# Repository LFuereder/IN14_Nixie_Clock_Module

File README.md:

# IN14-Nixie Tube Clock Module
This project contains the schematics, software implementation and documentation for a clock displaying the current time on nixie-tubes. The clock utilizes a GigaDevices GD32L233 microcontroller (ARM Cortex-M33), which triggers the displayed digits in the tubes via voltage-domain separation through LTV-352T optocouplers. 

The current design is planned to display hours and minutes, but it can be extended to display the seconds as well. 

The general structure of the project is as follows:
```
IN14_Nixie_Clock_Module/
|-- 01_Circuit_Board/
|-- 02_Software/
|-- 03_Datasheets/
```
In the folder `01_Circuit_Board` you can find all relevant files for the hardware part of this project. This includes the KiCAD project, footprints for the custom components and the CAD script for the custom tube socket. In folder `02_Software` you can find the implementation of the clock. As this is a module, the Board can be used as standalone application (although this does not make much sense, since you need at least two PCBs to display the current time) or as a set of two to display hour and minutes. A clock consisting of three boards is currently not supported, but can be extended in the future. Lastly in `03_Datasheets` you can find further information about the components in use. 

# Finished Prototype
The current prototype of a finished implementation of the clock is displayed in the figure below.

For the wiring between the modules and the DCDC-converter please consider the following image:

Since this is a prototype, we used dupont crimp connectors and wago cage clamps. In a finished product these could be replaced by fixed/soldered wires.

# Contributing
I would like to thank [@LStromaier](https://github.com/LStrohmaier) for working along side me on this project and reviewing most of the hardware and software implemenatations.

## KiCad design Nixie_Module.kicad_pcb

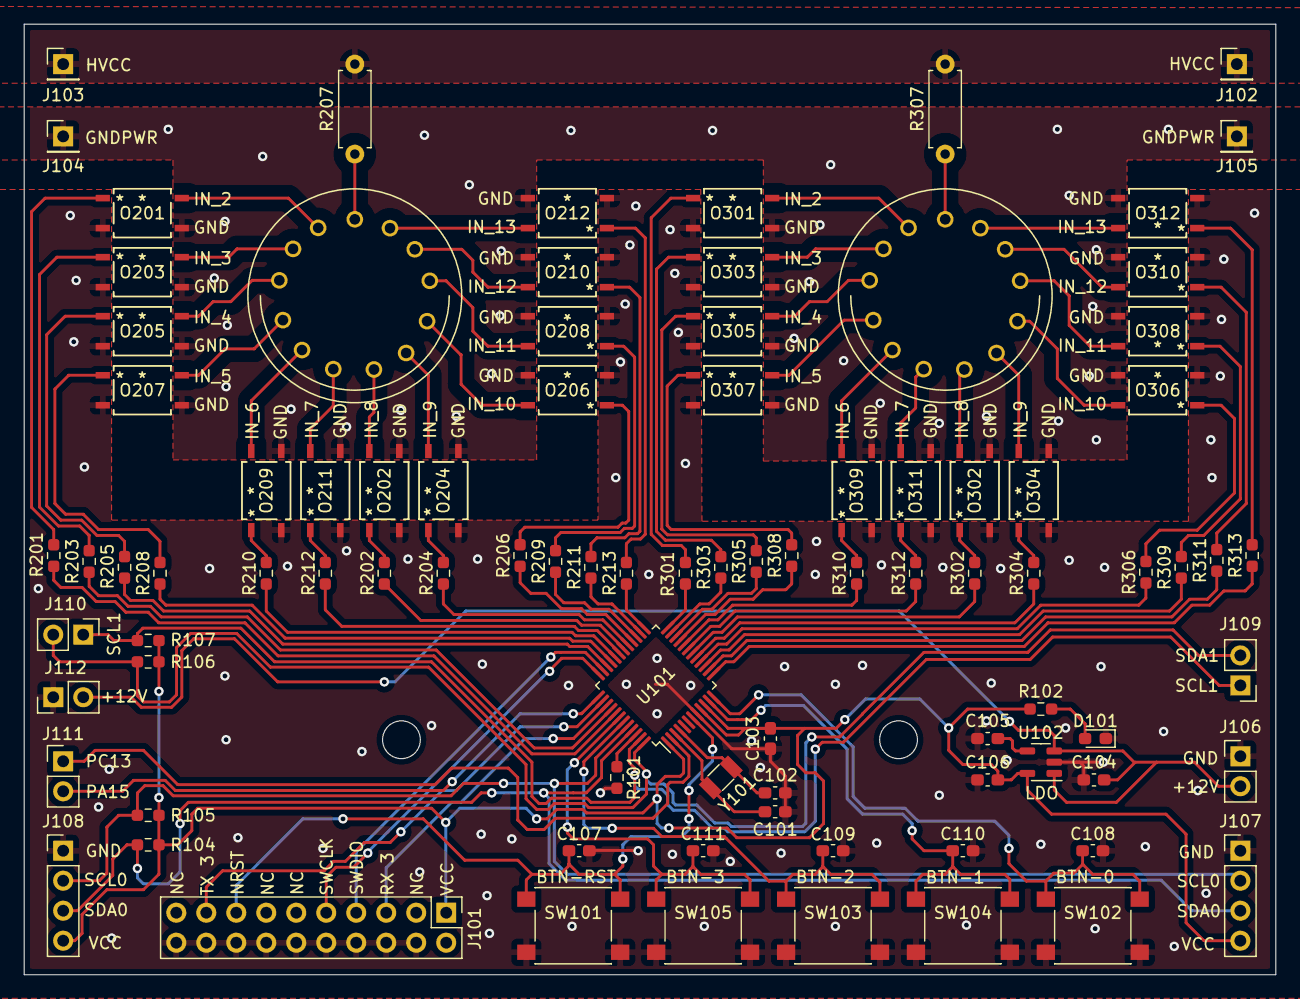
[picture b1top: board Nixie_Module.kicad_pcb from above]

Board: 2 copper layers, 106.0 x 80.5 mm, 90 parts (0 on the bottom side), 99 nets.

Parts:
C101, C102, C103, C104, C106, C107, C108, C109, C110, C111: 1u; C_0603_1608Metric_Pad1.08x0.95mm_HandSolder
C105: 470p; C_0603_1608Metric_Pad1.08x0.95mm_HandSolder
D101: LED; D_0603_1608Metric_Pad1.05x0.95mm_HandSolder
J101: JTAG_CON; PinHeader_2x10_P2.54mm_Vertical
J102: HV-IN; PinHeader_1x01_P2.54mm_Vertical
J103: HV-OUT; PinHeader_1x01_P2.54mm_Vertical
J104: HVGND-OUT; PinHeader_1x01_P2.54mm_Vertical
J105: HVGND-IN; PinHeader_1x01_P2.54mm_Vertical
J106: 12V-OUT; PinHeader_1x02_P2.54mm_Vertical
J107: Prime-CON-IN; PinHeader_1x04_P2.54mm_Vertical
J108: Prime-CON-OUT; PinHeader_1x04_P2.54mm_Vertical
J109: Sec-CON-IN; PinHeader_1x02_P2.54mm_Vertical
J110: Sec-CON-OUT; PinHeader_1x02_P2.54mm_Vertical
J111: GPIO_Con; PinHeader_1x02_P2.54mm_Vertical
J112: 12V-IN; PinHeader_1x02_P2.54mm_Vertical
O201, O202, O203, O204, O205, O206, O207, O208, O209, O210, O211, O212, O301, O302, O303, O304, O305, O306, O307, O308, O309, O310, O311, O312: LTV-352T; IC4_LTV-352T_LTO
R101, R104, R105, R106, R107: 5k6R; R_0603_1608Metric_Pad0.98x0.95mm_HandSolder
R102: 300R; R_0603_1608Metric_Pad0.98x0.95mm_HandSolder
R201, R202, R203, R204, R205, R206, R208, R209, R210, R211, R212, R213, R301, R302, R303, R304, R305, R306, R308, R309, R310, R311, R312, R313: 154R; R_0603_1608Metric_Pad0.98x0.95mm_HandSolder
R207, R307: 69kR; R_Axial_DIN0207_L6.3mm_D2.5mm_P7.62mm_Horizontal
SW101: RST-BTN; SW_Push_1P1T_NO_6x6mm_H9.5mm
SW102: BTN0; SW_Push_1P1T_NO_6x6mm_H9.5mm
SW103: BTN2; SW_Push_1P1T_NO_6x6mm_H9.5mm
SW104: BTN1; SW_Push_1P1T_NO_6x6mm_H9.5mm
SW105: BTN3; SW_Push_1P1T_NO_6x6mm_H9.5mm
TBE201, TBE301: IN14; IN-14_Nixie
U101: LQFP-48_7x7mm_P0.5mm
U102: MIC5219-3.3YM5; SOT-23-5
Y101: Crystal; Crystal_SMD_3215-2Pin_3.2x1.5mm

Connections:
+3.3V: C103.2, C106.1, J101.1 (VTREF), J107.4, J108.4, R102.2, R104.1, R105.2, R106.1, R107.2, U101.1 (VBAT), U101.9 (VREFP), U101.10 (VDD), U102.5 (OUT)
+12V: C104.1, J106.2, J112.2, U102.1 (IN), U102.3 (EN)
/1_OC_1: R201.1, U101.41 (PB3)
/1_OC_2: R203.1, U101.40 (PC12)
/1_OC_3: R205.1, U101.34 (PA12)
/1_OC_4: R208.1, U101.33 (PA11)
/1_OC_5: R210.1, U101.32 (PA10)
/1_OC_6: R212.1, U101.31 (PA9)
/1_OC_7: R202.1, U101.30 (PA8)
/1_OC_8: R204.1, U101.29 (PC7)
/1_OC_9: R206.1, U101.28 (PC6)
/1_OC_10: R209.1, U101.27 (PB15)
/1_OC_11: R211.1, U101.26 (PB14)
/1_OC_12: R213.1, U101.25 (PB13)
/2_OC_1: R301.1, U101.24 (PB12)
/2_OC_2: R303.1, U101.23 (PB11)
/2_OC_3: R305.1, U101.22 (PB10)
/2_OC_4: R308.1, U101.21 (BOOT1-PB2)
/2_OC_5: R310.1, U101.20 (PB1)
/2_OC_6: R312.1, U101.19 (PB0)
/2_OC_7: R302.1, U101.18 (PA7)
/2_OC_8: R304.1, U101.17 (PA6)
/2_OC_9: R306.1, U101.16 (PA5)
/2_OC_10: R309.1, U101.15 (PA4)
/2_OC_11: R311.1, U101.14 (PA3)
/2_OC_12: R313.1, U101.13 (PA2)
/BOOT0: R101.1, U101.46 (BOOT0-PD3)
/BTN0: C108.1, SW102.1, U101.12 (PA1)
/BTN1: C110.1, SW104.1, U101.11 (PA0)
/BTN2: C109.1, SW103.1, U101.43 (PB5)
/BTN3: C111.1, SW105.1, U101.42 (PB4)
/IN14_1/1_IN14_2: O201.4, TBE201.2 (.Comma)
/IN14_1/1_IN14_3: O203.4, TBE201.3 (C1)
/IN14_1/1_IN14_4: O205.4, TBE201.4 (C2)
/IN14_1/1_IN14_5: O207.4, TBE201.5 (C3)
/IN14_1/1_IN14_6: O209.4, TBE201.6 (C4)
/IN14_1/1_IN14_7: O211.4, TBE201.7 (C5)
/IN14_1/1_IN14_8: O202.4, TBE201.8 (C6)
/IN14_1/1_IN14_9: O204.4, TBE201.9 (C7)
/IN14_1/1_IN14_10: O206.4, TBE201.10 (C8)
/IN14_1/1_IN14_11: O208.4, TBE201.11 (C9)
/IN14_1/1_IN14_12: O210.4, TBE201.12 (C0)
/IN14_1/1_IN14_13: O212.4, TBE201.13 (Comma.)
/IN14_2/2_IN14_2: O301.4, TBE301.2 (.Comma)
/IN14_2/2_IN14_3: O303.4, TBE301.3 (C1)
/IN14_2/2_IN14_4: O305.4, TBE301.4 (C2)
/IN14_2/2_IN14_5: O307.4, TBE301.5 (C3)
/IN14_2/2_IN14_6: O309.4, TBE301.6 (C4)
/IN14_2/2_IN14_7: O311.4, TBE301.7 (C5)
/IN14_2/2_IN14_8: O302.4, TBE301.8 (C6)
/IN14_2/2_IN14_9: O304.4, TBE301.9 (C7)
/IN14_2/2_IN14_10: O306.4, TBE301.10 (C8)
/IN14_2/2_IN14_11: O308.4, TBE301.11 (C9)
/IN14_2/2_IN14_12: O310.4, TBE301.12 (C0)
/IN14_2/2_IN14_13: O312.4, TBE301.13 (Comma.)
/NRST: C107.1, J101.15 (~SRST), SW101.1, U101.7 (NRST)
/PA15: J111.2, U101.37 (PA15)
/PC13: J111.1, U101.2 (PC13)
/SCL0/UART0_TX: J107.2, J108.2, R105.1, U101.44 (PB6)
/SCL1: J109.1, J110.1, R107.1, U101.47 (PB8)
/SDA0/UART0_RX: J107.3, J108.3, R104.2, U101.45 (PB7)
/SDA1: J109.2, J110.2, R106.2, U101.48 (PB9)
/SWCLK: J101.9 (TCK/SWDCLK), U101.36 (PA14)
/SWDIO: J101.7 (TMS/SWDIO), U101.35 (PA13)
/UART3_RX: J101.5 (TDI/UART-Tx), U101.39 (PC11)
/UART3_TX: J101.17 (DBGRQ/UART-Rx), U101.38 (PC10)
GND: C101.2, C102.2, C103.1, C104.2, C105.2, C106.2, C107.2, C108.2, C109.2, C110.2, C111.2, D101.1 (K), J101.4 (GND), J101.6 (GND), J101.8 (GND), J101.10 (GND), J101.12 (GND), J101.14 (GND), J101.16 (GND), J101.18 (GND), J101.20 (GND), J106.1, J107.1, J108.1, J112.1, O201.2, O202.2, O203.2, O204.2, O205.2, O206.2, O207.2, O208.2, O209.2, O210.2, O211.2, O212.2, O301.2, O302.2, O303.2, O304.2, O305.2, O306.2, O307.2, O308.2, O309.2, O310.2, O311.2, O312.2, R101.2, SW101.2, SW102.2, SW103.2, SW104.2, SW105.2, U101.8 (VSS), U102.2 (GND)
GNDPWR: J104.1, J105.1, O201.3, O202.3, O203.3, O204.3, O205.3, O206.3, O207.3, O208.3, O209.3, O210.3, O211.3, O212.3, O301.3, O302.3, O303.3, O304.3, O305.3, O306.3, O307.3, O308.3, O309.3, O310.3, O311.3, O312.3
HVCC: J102.1, J103.1, R207.2, R307.2
unnamed: D101.2 (A), R102.1
unnamed: O201.1, R201.2
unnamed: O202.1, R202.2
unnamed: O203.1, R203.2
unnamed: O204.1, R204.2
unnamed: O205.1, R205.2
unnamed: O206.1, R206.2
unnamed: O207.1, R208.2
unnamed: O208.1, R209.2
unnamed: O209.1, R210.2
unnamed: O210.1, R211.2
unnamed: O211.1, R212.2
unnamed: O212.1, R213.2
unnamed: O301.1, R301.2
unnamed: O302.1, R302.2
unnamed: O303.1, R303.2
unnamed: O304.1, R304.2
unnamed: O305.1, R305.2
unnamed: O306.1, R306.2
unnamed: O307.1, R308.2
unnamed: O308.1, R309.2
unnamed: O309.1, R310.2
unnamed: O310.1, R311.2
unnamed: O311.1, R312.2
unnamed: O312.1, R313.2
unnamed: R207.1, TBE201.1 (Anode)
unnamed: R307.1, TBE301.1 (Anode)
unnamed: C101.1, U101.3 (PC14), Y101.1
unnamed: C102.1, U101.4 (PC15), Y101.2
unnamed: C105.1, U102.4 (BP)

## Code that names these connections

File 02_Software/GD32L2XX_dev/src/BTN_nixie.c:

#include "../inc/BTN_nixie.h"

#define SYSCTL_EXTI_SS1_PB4     0x40010000U

/* Global variables for clock configuration */
extern uint8_t config_state;
extern rtc_parameter_struct current_time; 

/* Global indicator, weather the controller 
   shall display minutes or hours. */
extern bool show_minutes;


/* Since the RTC initialisation expects BCD format, 
   we need to adjust the number interpretation from 
   10-basis to 16-basis. I.e., config_minute = 12 needs
   to be interpreted as 0x12. */
static uint8_t convert_to_BCD(uint8_t number)
{
    uint8_t decimal = (number / 10) << 4;
    uint8_t digit = (number % 10);
    return decimal + digit;
}

/* Since we need to adjust the current time in the 
   config mode in decimal, we need a function to 
   convert the current time back to decimal. */
static uint8_t convert_to_DEC(uint8_t number)
{
    uint8_t decimal = (number / 16) * 10;
    uint8_t digit = (number % 16);
    return decimal + digit;
}

/* The Button 3 handler serves as a configuration 
   mode for the clock. If the button is tapped, the 
   clock shall display the current values of hour 
   and minute and wait for termination via Button 0. */
void btn_3_irq_handler()
{
    /* set config state bit to switch to configuration mode. If it should 
    be switched back, press BTN_0 (see btn_0_irq_handler())*/
    config_state = 1;

    while(config_state == 1)
    {
        reset_tube(NIXIE_IN14_1);
        reset_tube(NIXIE_IN14_2);

        display_time(&current_time, show_minutes);
    }
    
#if ENABLE_COM
        if(show_minutes)
        {
            transmit_current_time(current_time.minute);
        }
        else
        {
            transmit_current_time(current_time.hour);
        }
#endif

    init_RTC(current_time);
    return;
}

/* The Button 2 handler reduces the value of the 
   currently displayed number. */
void btn_2_irq_handler()
{
    if(show_minutes)
    {
        if(current_time.minute > 0)
        {
            uint8_t current_minute = convert_to_DEC(current_time.minute);
            current_minute--;
            current_time.minute = convert_to_BCD(current_minute);
        }
        else
        {
            current_time.minute = convert_to_BCD(59);
        }
    }
    else
    {
        if(current_time.hour > 0)
        {
            uint8_t current_hour = convert_to_DEC(current_time.hour);
            current_hour--;
            current_time.hour = convert_to_BCD(current_hour);
        }
        else
        {
            current_time.hour = convert_to_BCD(23);
        }
    }
    
    return;
}

/* The Button 1 handler increases the value of the 
   currently display number. */
void btn_1_irq_handler()
{
    if(show_minutes)
    {
        if(current_time.minute < convert_to_BCD(59)) 
        {
            uint8_t current_minute = convert_to_DEC(current_time.minute);
            current_minute++;
            current_time.minute = convert_to_BCD(current_minute);
        }
        else 
        {
            current_time.minute = 0;
        }
    }
    else
    {
        if(current_time.hour < convert_to_BCD(23)) 
        {
            uint8_t current_hour = convert_to_DEC(current_time.hour);
            current_hour++;
            current_time.hour = convert_to_BCD(current_hour);
        }
        else 
        {
            current_time.hour = 0;
        }
    }

    return;
}

/* The Button 9 handler terminates the configuration 
   mode of the clock by setting the config_state 
   value to zero. */
void btn_0_irq_handler()
{
    config_state = 0;
    return;
}

/* Initializes and enables the EXTI-IRQ for the line 
   of pins passed as parameter. */
static void configure_btn_irq(exti_line_enum linex)
{
    exti_init(linex, EXTI_INTERRUPT, EXTI_TRIG_FALLING);
    exti_flag_clear(linex);
    exti_interrupt_enable(linex);
}

/* Entry function, which initializes and enables all 
   buttons on the nixie watch pcb. Furthermore, enables 
   the external interrupts to call the handler of each 
   button. */
void init_buttons()
{
    RCU_APB2EN |= 0x01;

    /* Configure all Buttons as input */

    /* BTN-1 (PA0) button setup */
    gpio_mode_set(GPIOA, GPIO_MODE_INPUT, GPIO_PUPD_PULLUP, GPIO_PIN_0);
    syscfg_exti_line_config(EXTI_SOURCE_GPIOA, EXTI_SOURCE_PIN0);
    configure_btn_irq(EXTI_0);
    nvic_irq_enable(EXTI0_IRQn, 1);

    /* BTN-0 (PA1) button setup */
    gpio_mode_set(GPIOA, GPIO_MODE_INPUT, GPIO_PUPD_PULLUP, GPIO_PIN_1);
    syscfg_exti_line_config(EXTI_SOURCE_GPIOA, EXTI_SOURCE_PIN1);
    configure_btn_irq(EXTI_1);
    nvic_irq_enable(EXTI1_IRQn, 0);

    /* BTN-3 (PB4) button setup */
    gpio_mode_set(GPIOB, GPIO_MODE_INPUT, GPIO_PUPD_PULLUP, GPIO_PIN_4);
    syscfg_exti_line_config(EXTI_SOURCE_GPIOB, EXTI_SOURCE_PIN4);
    configure_btn_irq(EXTI_4);
    nvic_irq_enable(EXTI4_IRQn, 3);
    
    /* BTN-2 (PB5) button setup */
    gpio_mode_set(GPIOB, GPIO_MODE_INPUT, GPIO_PUPD_PULLUP, GPIO_PIN_5);
    syscfg_exti_line_config(EXTI_SOURCE_GPIOB, EXTI_SOURCE_PIN5);
    configure_btn_irq(EXTI_5);
    nvic_irq_enable(EXTI5_9_IRQn, 2);   
}

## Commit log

2025-02-07 migrated nixie_clock repository from GitLab to GitHub.
2025-02-07 Restructured entire repository to increase usability and define fundamental structure of the project.
2025-02-07 identical to the backup folder, deleted the redundant KiCAD project .
2025-10-24 minor changes in the clock software.
2025-10-26 fixed build environment and adjusted build script.
2025-10-26 implemented initial version of the configuration mode of the nixie clock module.
2025-10-27 fixed minute and hour switch relative to the boolean indicator.
2025-10-29 reduced HAL depependency to BTN_nixie file to external declared irq-handler.
2025-10-29 removed 24h digit display bug. Additionally fixed bcd conversion bug and reduced unused variables from the software implementation.
2025-11-09 added mirror layout support for sockets on the back of the pcb.
2025-11-12 minor bug fixes to correctly display the timeValues and correct transmission.
2025-11-15 removed redundant config_hour and config_minute variables from the implementation and fixed couple of bugs in the course of implementation.
2025-11-15 added new configuration header file to set global defines for the entire application.
2025-11-15 Wrote commentary for the entire application.
2025-11-15 restructured the software implementation directory.
2025-11-15 added commentary in the main.c.
2025-11-16 restructured the UART configuration interface and and cleaned up the main.c file.
2025-11-16 renamed socket folder.
2025-11-16 added README.md file for the project.
2025-11-16 added initial version of the software readme.md.
2025-11-16 wrote initial version of the 02_Software README.md.
2025-11-16 adjusted size of the software design image.
2025-11-17 Add LICENSE file
2025-11-17 added apache license notice to the source files
2025-11-17 added Apache License to the hardware implementation.
2025-11-18 signed Apache 2.0 license term.
2025-11-18 added 02_Software directory structure to the README.md.
